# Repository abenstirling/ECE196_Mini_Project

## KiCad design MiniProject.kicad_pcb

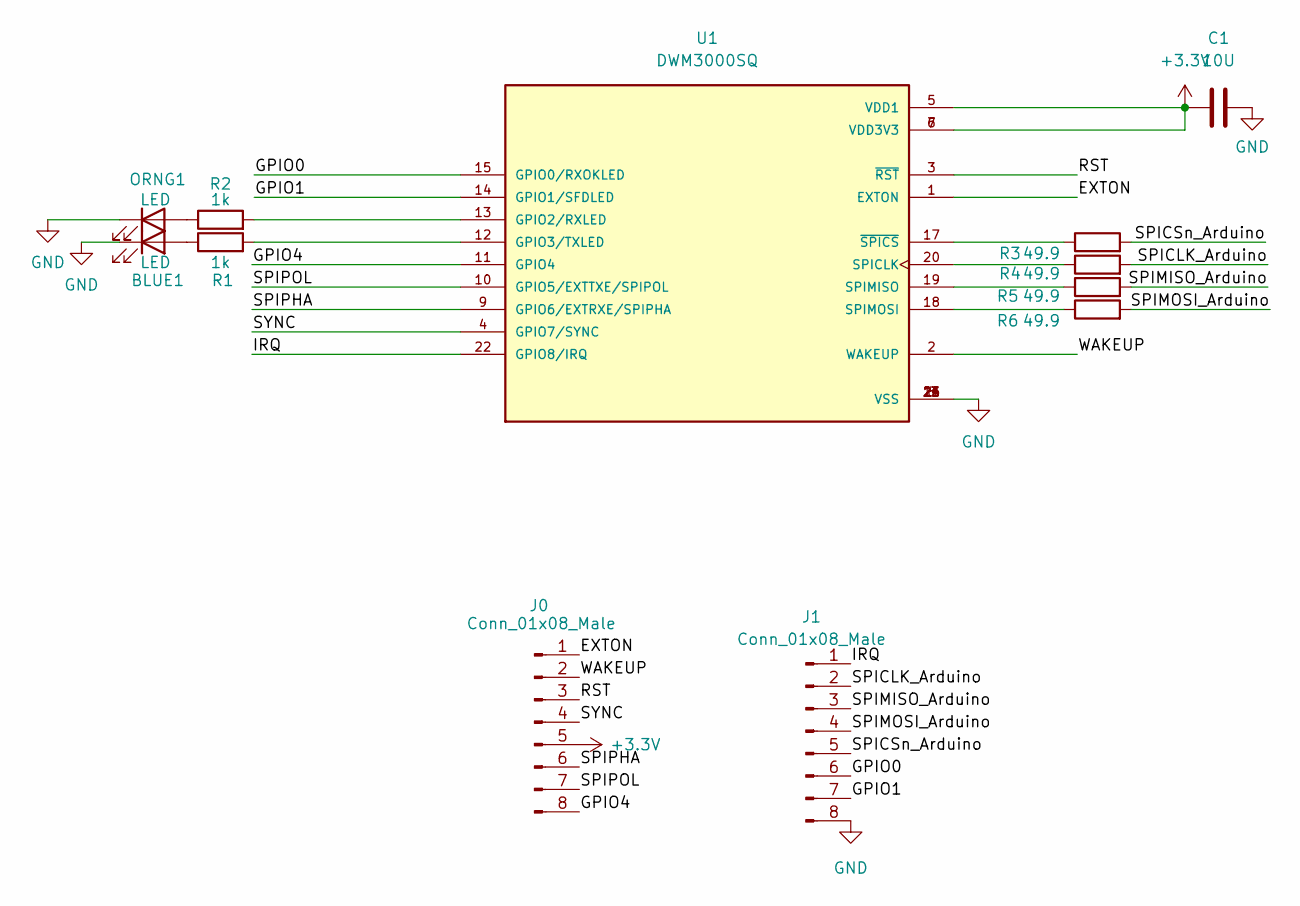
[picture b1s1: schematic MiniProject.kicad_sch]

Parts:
BLUE1: LED; LED_0603_1608Metric
C1: 10U; C_0603_1608Metric
J0, J1: Conn_01x08_Male; PinHeader_1x08_P2.54mm_Vertical
ORNG1: LED; LED_0603_1608Metric
R1, R2: 1k; R_0603_1608Metric
R3, R4, R5, R6: 49.9; R_0603_1608Metric
U1: DWM3000SQ; XCVR_DWM3000SQ; PARTREV B

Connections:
+3.3V: C1.1, J0.5, U1.5 (VDD1), U1.6 (VDD3V3), U1.7 (VDD3V3)
/EXTON: J0.1, U1.1 (EXTON)
/GPIO0: J1.6, U1.15 (GPIO0/RXOKLED)
/GPIO1: J1.7, U1.14 (GPIO1/SFDLED)
/GPIO4: J0.8, U1.11 (GPIO4)
/IRQ: J1.1, U1.22 (GPIO8/IRQ)
/RST: J0.3, U1.3 (~RST)
/SPICLK_Arduino: J1.2, R4.2
/SPICSn_Arduino: J1.5, R3.2
/SPIMISO_Arduino: J1.3, R5.2
/SPIMOSI_Arduino: J1.4, R6.2
/SPIPHA: J0.6, U1.9 (GPIO6/EXTRXE/SPIPHA)
/SPIPOL: J0.7, U1.10 (GPIO5/EXTTXE/SPIPOL)
/SYNC: J0.4, U1.4 (GPIO7/SYNC)
/WAKEUP: J0.2, U1.2 (WAKEUP)
GND: BLUE1.1 (K), C1.2, J1.8, ORNG1.1 (K), U1.8 (VSS), U1.16 (VSS), U1.21 (VSS), U1.23 (VSS), U1.24 (VSS)
unnamed: ORNG1.2 (A), R2.1
unnamed: BLUE1.2 (A), R1.1
unnamed: R1.2, U1.12 (GPIO3/TXLED)
unnamed: R2.2, U1.13 (GPIO2/RXLED)
unnamed: R3.1, U1.17 (~SPICS)
unnamed: R4.1, U1.20 (SPICLK)
unnamed: R5.1, U1.19 (SPIMISO)
unnamed: R6.1, U1.18 (SPIMOSI)

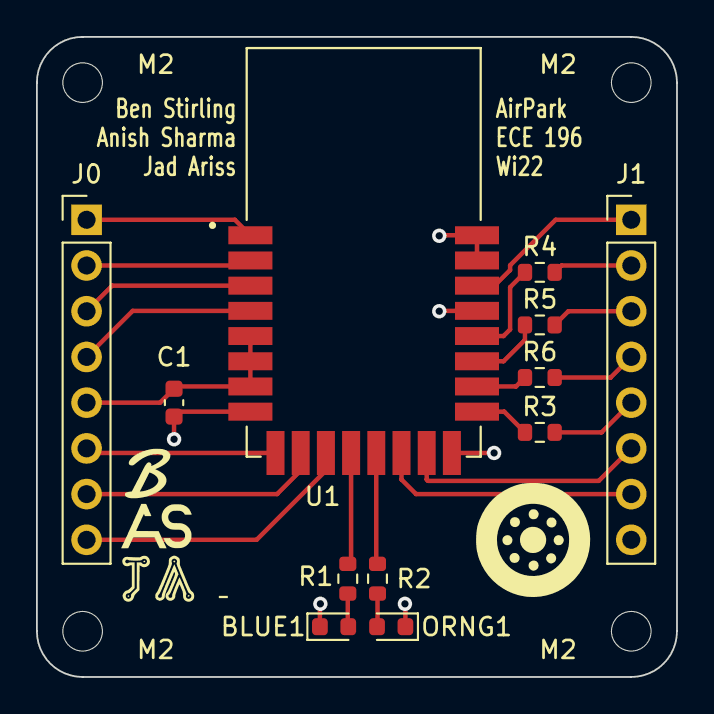
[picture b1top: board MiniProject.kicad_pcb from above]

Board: 2 copper layers, 35.6 x 35.6 mm, 16 parts (0 on the bottom side), 24 nets.

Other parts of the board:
M2, M2#2, M2#3, M2#4: MountingHole_2.2mm_M2

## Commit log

2023-02-10 With Exports
